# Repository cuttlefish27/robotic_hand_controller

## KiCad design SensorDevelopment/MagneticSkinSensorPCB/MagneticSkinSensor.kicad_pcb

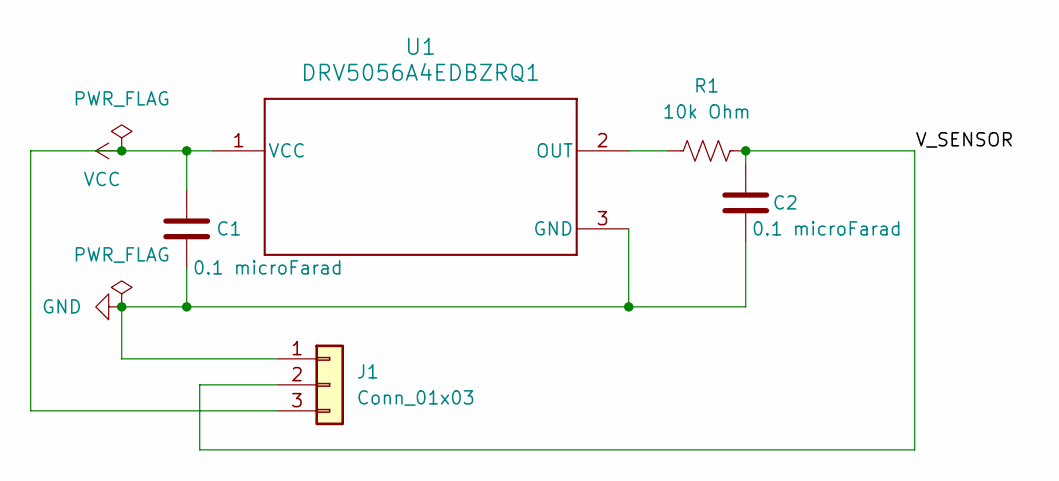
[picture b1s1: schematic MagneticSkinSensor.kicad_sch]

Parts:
C1, C2: 0.1 microFarad; C_0603_1608Metric
J1: Conn_01x03; PinHeader_1x03_P2.54mm_Horizontal
R1: 10k Ohm; R_0603_1608Metric
U1: DRV5056A4EDBZRQ1; DBZ0003A_M

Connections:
/V_SENSOR: C2.1, J1.2, R1.2
GND: C1.2, C2.2, J1.1, U1.3 (GND)
unnamed: R1.1, U1.2 (OUT)
VCC: C1.1, J1.3, U1.1 (VCC)

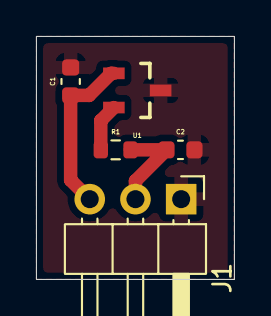
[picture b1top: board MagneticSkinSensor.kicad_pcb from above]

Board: 2 copper layers, 11.0 x 13.5 mm, 5 parts (0 on the bottom side), 4 nets.
